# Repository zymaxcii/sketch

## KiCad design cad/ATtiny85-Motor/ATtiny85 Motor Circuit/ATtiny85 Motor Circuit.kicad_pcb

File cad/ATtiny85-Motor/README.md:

# ATtiny85-Motor

These are all the files that I used to make a ATtiny85 circuit that controls a motor's speed using a potentiometer, and also has indicator LEDs to qualitatively show the speed as you turn the potentiometer.

One thing to note is that for some reason the footprint for the diode D1 is backwards in KiCAD so when I first tried building this circuit the transistor would get very hot and after reversing the diode, the circuit worked properly.

I made a short youtube video to demonstrate this: https://www.youtube.com/watch?v=jHjCyNegOxA

https://github.com/The-Invent0r/ATtiny85-Motor/tree/main

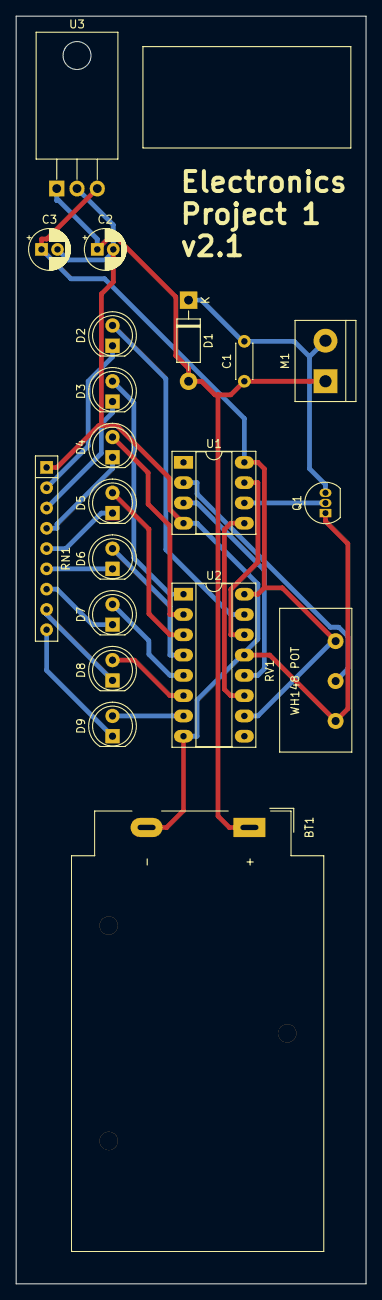
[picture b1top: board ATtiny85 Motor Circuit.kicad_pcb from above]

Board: 2 copper layers, 43.8 x 158.8 mm, 20 parts (0 on the bottom side), 25 nets.

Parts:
BT1: Battery_Cell; BatteryHolder_MPD_BA9VPC_1xPP3
C1: C; C_Disc_D4.3mm_W1.9mm_P5.00mm
C2, C3: CP1; CP_Radial_D5.0mm_P2.00mm
D1: DIODE; D_DO-41_SOD81_P10.16mm_Horizontal
D2, D3, D4, D5, D6, D7, D8, D9: LED; LED_D5.0mm
M1: Motor_DC; TerminalBlock_bornier-2_P5.08mm
Q1: 2N7000; TO-92_Inline
RN1: R_Network08; R_Array_SIP9
RV1: R_POT; Potentiometer_WH148
U1: ATtiny85-20PU; DIP-8_W7.62mm_Socket_LongPads
U2: 74HC595; DIP-16_W7.62mm_Socket_LongPads
U3: L7805; TO-220-3_Horizontal_TabDown

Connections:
GND: BT1.2, C2.2, C3.2, Q1.1, RN1.1, RV1.1, U1.4, U2.8, U2.13, U3.2
unnamed: BT1.1, C1.1, C2.1, D1.2, M1.1, U3.1
unnamed: C1.2, D1.1, M1.2, Q1.3
unnamed: D2.1, RN1.2
unnamed: D2.2, U2.15
unnamed: D3.1, RN1.3
unnamed: D3.2, U2.1
unnamed: D4.1, RN1.4
unnamed: D4.2, U2.2
unnamed: D5.1, RN1.5
unnamed: D5.2, U2.3
unnamed: D6.1, RN1.6
unnamed: D6.2, U2.4
unnamed: D7.1, RN1.7
unnamed: D7.2, U2.5
unnamed: D8.1, RN1.8
unnamed: D8.2, U2.6
unnamed: D9.1, RN1.9
unnamed: D9.2, U2.7
unnamed: Q1.2, U1.6
unnamed: RV1.2, U1.2
unnamed: U1.3, U2.12
unnamed: U1.5, U2.11
unnamed: U1.7, U2.14
VCC: C3.1, RV1.3, U1.8, U2.10, U2.16, U3.3

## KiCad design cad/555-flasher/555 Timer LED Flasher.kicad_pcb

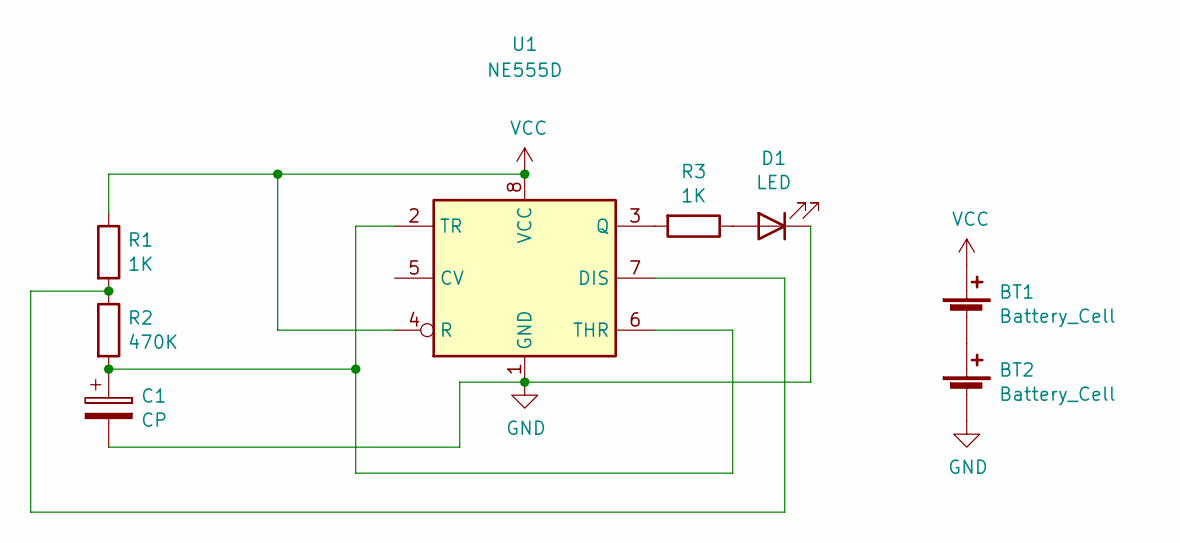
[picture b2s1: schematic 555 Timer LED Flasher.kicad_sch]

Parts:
BT1, BT2: Battery_Cell; BatteryHolder_LINX_BAT-HLD-012-SMT
C1: CP; CP_Elec_4x3
D1: LED; LED_0805_2012Metric
R1, R3: 1K; R_01005_0402Metric
R2: 470K; R_01005_0402Metric
U1: NE555D; SOIC-8_3.9x4.9mm_P1.27mm

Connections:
GND: BT2.2 (-), C1.2, D1.1 (K), U1.1 (GND)
unnamed: BT1.2 (-), BT2.1 (+)
unnamed: C1.1, R2.2, U1.2 (TR), U1.6 (THR)
unnamed: D1.2 (A), R3.1
unnamed: R1.2, R2.1, U1.7 (DIS)
unnamed: R3.2, U1.3 (Q)
VCC: BT1.1 (+), R1.1, U1.4 (R), U1.8 (VCC)

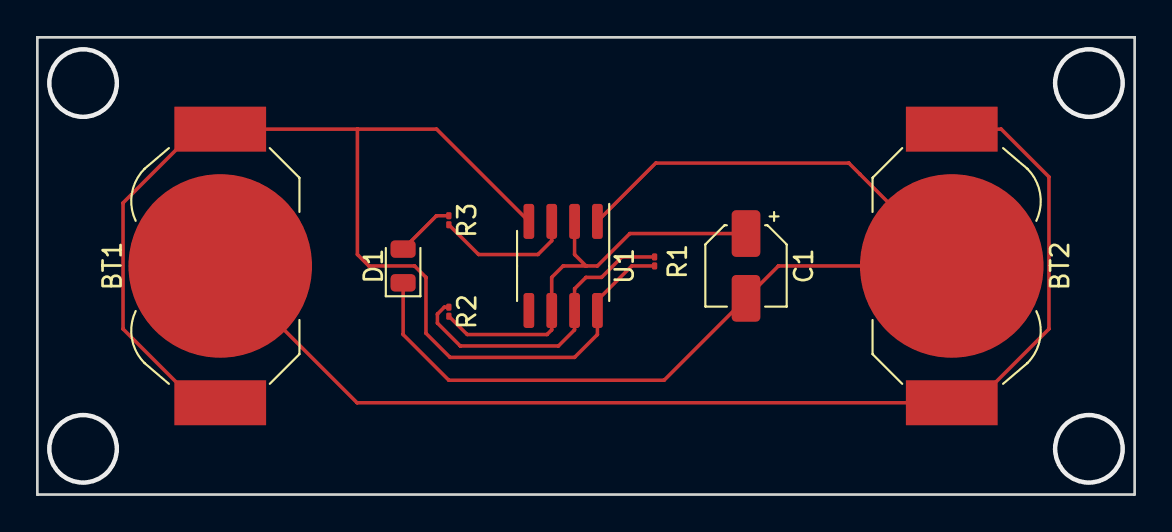
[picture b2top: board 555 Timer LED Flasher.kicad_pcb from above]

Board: 2 copper layers, 61.0 x 25.4 mm, 8 parts (0 on the bottom side), 7 nets.

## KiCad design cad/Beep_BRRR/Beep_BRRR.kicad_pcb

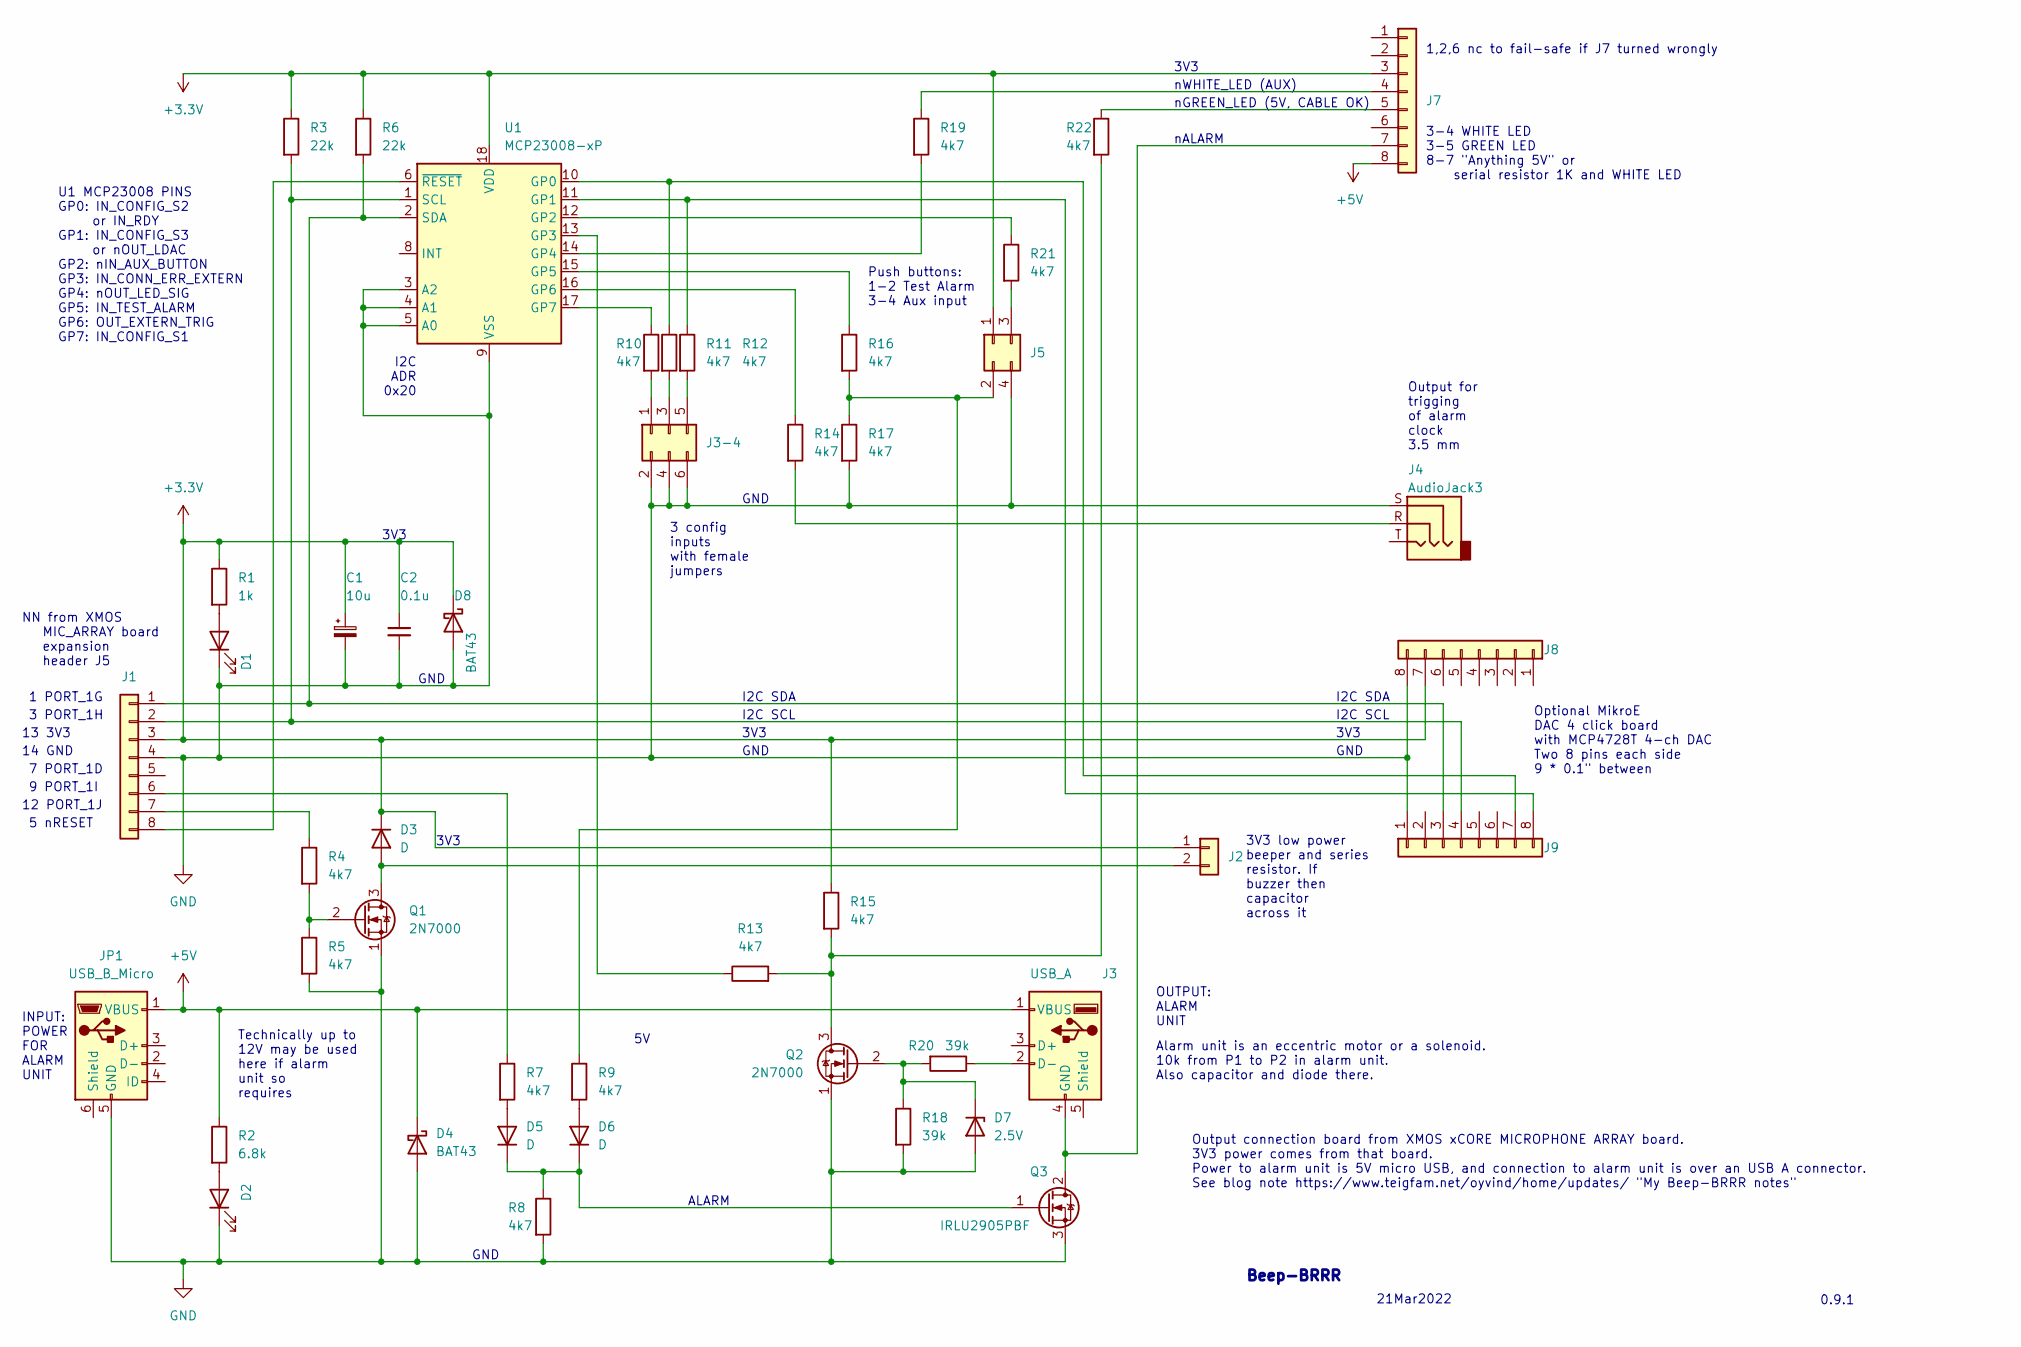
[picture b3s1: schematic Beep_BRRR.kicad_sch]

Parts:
C1: 10u; CP_Radial_D5.0mm_P2.50mm
C2: 0.1u; C_Disc_D3.4mm_W2.1mm_P2.50mm
D1, D2: LED; LED_D3.0mm
D3, D5, D6: D; D_A-405_P2.54mm_Vertical_KathodeUp
D4, D8: BAT43; D_A-405_P2.54mm_Vertical_KathodeUp
D7: 2.5V; D_A-405_P2.54mm_Vertical_KathodeUp
J1: Conn_01x08; PinHeader_1x08_P2.54mm_Vertical
J2: Conn_01x02; PinHeader_1x02_P2.54mm_Vertical
J3: USB_A; USB_A_Molex_67643_Horizontal
J3-4: Conn_02x03_Odd_Even; PinHeader_2x03_P2.54mm_Vertical
J4: AudioJack3; Jack_3.5mm_CUI_SJ1-3533NG_Horizontal_CircularHoles
J5: Conn_02x02_Odd_Even; PinHeader_2x02_P2.54mm_Vertical
J7, J8, J9: Conn_01x08; PinSocket_1x08_P2.54mm_Vertical
JP1: USB_B_Micro; USB_Micro-AB_Molex_47590-0001
Q1, Q2: 2N7000; TO-92_Inline
Q3: IRLU2905PBF; TO-251-3_Vertical
R1: 1k; R_Axial_DIN0204_L3.6mm_D1.6mm_P2.54mm_Vertical
R2: 6.8k; R_Axial_DIN0204_L3.6mm_D1.6mm_P2.54mm_Vertical
R3, R6: 22k; R_Axial_DIN0204_L3.6mm_D1.6mm_P2.54mm_Vertical
R4, R5, R7, R8, R9, R10, R11, R12, R13, R14, R15, R16, R17, R19, R21, R22: 4k7; R_Axial_DIN0204_L3.6mm_D1.6mm_P2.54mm_Vertical
R18, R20: 39k; R_Axial_DIN0204_L3.6mm_D1.6mm_P2.54mm_Vertical
U1: MCP23008-xP; DIP-18_W7.62mm

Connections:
+3V3: C1.1, C2.1, D3.1 (K), D8.1 (K), J1.3, J2.1, J5.1, J7.3, J8.7, R1.1, R3.1, R6.1, R15.1, U1.18 (VDD)
+5V: D4.1 (K), J3.1 (VBUS), J7.8, JP1.1 (VBUS), R2.1
GND: C1.2, C2.2, D1.1 (K), D2.1 (K), D4.2 (A), D7.2 (A), D8.2 (A), J1.4, J3-4.2, J3-4.4, J3-4.6, J4.S, J5.4, J8.8, J9.1, JP1.5 (GND), Q1.1 (S), Q2.1 (S), Q3.3 (S), R5.2, R8.2, R17.2, R18.2, U1.3 (A2), U1.4 (A1), U1.5 (A0), U1.9 (VSS)
unnamed: D1.2 (A), R1.2
unnamed: D2.2 (A), R2.2
unnamed: D3.2 (A), J2.2, Q1.3 (D)
unnamed: D5.1 (K), D6.1 (K), Q3.1 (G), R8.1
unnamed: D5.2 (A), R7.2
unnamed: D6.2 (A), R9.2
unnamed: D7.1 (K), Q2.2 (G), R18.1, R20.2
unnamed: J1.1, J9.3, R6.2, U1.2 (SDA)
unnamed: J1.2, J9.4, R3.2, U1.1 (SCL)
unnamed: J1.6, R7.1
unnamed: J1.7, R4.1
unnamed: J1.8, U1.6 (~RESET)
unnamed: J3-4.1, R10.2
unnamed: J3-4.3, R11.2
unnamed: J3-4.5, R12.2
unnamed: J3.2 (D-), R20.1
unnamed: J3.4 (GND), J7.7, Q3.2 (D)
unnamed: J4.R, R14.2
unnamed: J5.2, R9.1, R16.2, R17.1
unnamed: J5.3, R21.2
unnamed: J7.4, R19.1
unnamed: J7.5, R22.1
unnamed: Q1.2 (G), R4.2, R5.1
unnamed: R10.1, U1.17 (GP7)
unnamed: J9.7, R11.1, U1.10 (GP0)
unnamed: J9.8, R12.1, U1.11 (GP1)
unnamed: R13.1, U1.13 (GP3)
unnamed: Q2.3 (D), R13.2, R15.2, R22.2
unnamed: R14.1, U1.16 (GP6)
unnamed: R16.1, U1.15 (GP5)
unnamed: R19.2, U1.14 (GP4)
unnamed: R21.1, U1.12 (GP2)

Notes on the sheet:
NN from XMOS MIC_ARRAY board expansion header J5
GND
nWHITE_LED (AUX)
21Mar2022
3V3
3-4 WHITE LED 3-5 GREEN LED 8-7 "Anything 5V" or serial resistor 1K and WHITE LED
I2C ADR 0x20
5 nRESET
3 PORT_1H
Output connection board from XMOS xCORE MICROPHONE ARRAY board. 3V3 power comes from that board. Power to alarm unit is 5V micro USB, and connection to alarm unit is over an USB A connector. See blog note https://www.teigfam.net/oyvind/home/updates/ "My Beep-BRRR notes"
I2C SCL
ALARM
3V3 low power beeper and series resistor. If buzzer then capacitor across it
nALARM
1,2,6 nc to fail-safe if J7 turned wrongly
13 3V3
9 PORT_1I
Optional MikroE DAC 4 click board with MCP4728T 4-ch DAC Two 8 pins each side 9 * 0.1" between
Beep-BRRR
14 GND
0.9.1
Output for trigging of alarm clock 3.5 mm
I2C SDA
7 PORT_1D
OUTPUT: ALARM UNIT
Push buttons: 1-2 Test Alarm 3-4 Aux input
3 config inputs with female jumpers
U1 MCP23008 PINS GP0: IN_CONFIG_S2 or IN_RDY GP1: IN_CONFIG_S3 or nOUT_LDAC GP2: nIN_AUX_BUTTON GP3: IN_CONN_ERR_EXTERN GP4: nOUT_LED_SIG GP5: IN_TEST_ALARM GP6: OUT_EXTERN_TRIG GP7: IN_CONFIG_S1
INPUT: POWER FOR ALARM UNIT
12 PORT_1J
Alarm unit is an eccentric motor or a solenoid. 10k from P1 to P2 in alarm unit. Also capacitor and diode there.
Technically up to 12V may be used here if alarm unit so requires
1 PORT_1G
nGREEN_LED (5V, CABLE OK)

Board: 2 copper layers, 46 parts (0 on the bottom side), 35 nets, no tracks yet.

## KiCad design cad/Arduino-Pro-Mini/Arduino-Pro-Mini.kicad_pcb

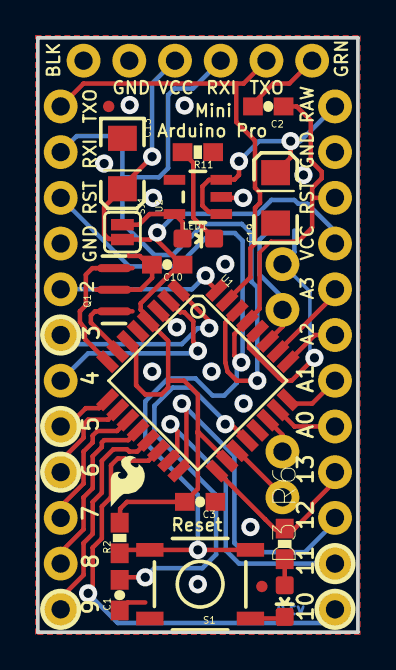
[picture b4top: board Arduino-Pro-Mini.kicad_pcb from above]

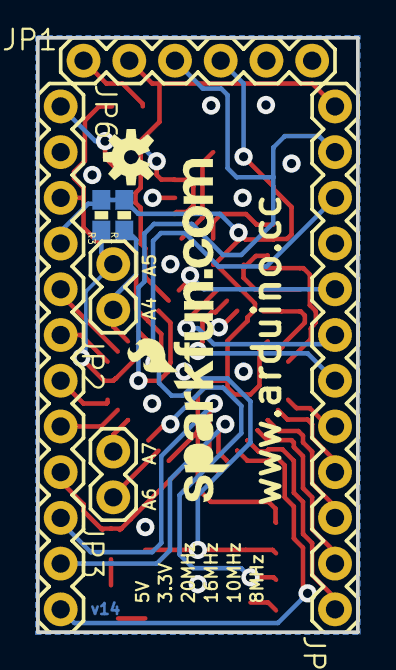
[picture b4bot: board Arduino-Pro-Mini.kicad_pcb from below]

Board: 2 copper layers, 17.8 x 33.0 mm, 29 parts (9 on the bottom side), 33 nets.

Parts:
C1, C2, C3, C10: 0.1uF; 0603-CAP
C13, C19: 10uF; EIA3216
D3: Green; 0603-LED-ALT1
FRAME1: FRAME-LETTER; CREATIVE_COMMONS
JP1: FTDI Basic; 1X06
JP2, JP3: 1X02
JP5, JP8: FIDUCIALUFIDUCIAL; MICRO-FIDUCIAL
JP6, JP7: 1X12
LED1: Red; 0603-LED-ALT1
Q1: 8/16/20MHz; RESONATOR-SMD-1_1
R1, R3: 0603-RES
R2, R11: 10K; 0603-RES
R6: 330; 0603-RES
S1: Reset; TACTILE-SWITCH-SMD-ALT01
SJ1: SJ_2S
U1: ATMEGA328; TQFP32-08
U2: MIC5205; SOT23-5
U$1: LOGO-SFESK; SFE-LOGO-FLAME
U$3: OSHW-LOGOS; OSHW-LOGO-S
U$11: LOGO-SFENEW; SFE-NEW-WEBLOGO

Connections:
A0: JP6.8, U1.23
A1: JP6.7, U1.24
A2: JP6.6, U1.25
A3: JP6.5, U1.26
A4: JP2.1, R1.1, U1.27
A5: JP2.2, R3.1, U1.28
A6: JP3.1, U1.19
A7: JP3.2, U1.22
AREF: C1.2, U1.20
D2: JP7.8, U1.32
D3: JP7.7, U1.1
D4: JP7.6, U1.2
D5: JP7.5, U1.9
D6: JP7.4, U1.10
D7: JP7.3, U1.11
D8: JP7.2, U1.12
D9: JP7.1, U1.13
D10: JP6.12, U1.14
DTR: C2.2, JP1.1
GND: C1.1, C3.1, C10.2, C13.C, C19.C, D3.C, JP1.5, JP1.6, JP6.2, JP7.9, Q1.2, R11.1, S1.1, S1.2, U1.3, U1.5, U1.21, U2.2
MISO: JP6.10, U1.16
MOSI: JP6.11, U1.15
unnamed: Q1.3, U1.8
unnamed: Q1.1, U1.7
unnamed: LED1.A, SJ1.1, U2.5
unnamed: LED1.C, R11.2
unnamed: D3.A, R6.2
RAW: C19.A, JP6.1, U2.1, U2.3
RESET: C2.1, JP6.3, JP7.10, R2.1, S1.3, S1.4, U1.29
RXI: JP1.3, JP7.11, U1.30
SCK: JP6.9, R6.1, U1.17
TXO: JP1.2, JP7.12, U1.31
VCC: C3.2, C10.1, C13.A, JP1.4, JP6.4, R1.2, R2.2, R3.2, SJ1.2, U1.4, U1.6, U1.18

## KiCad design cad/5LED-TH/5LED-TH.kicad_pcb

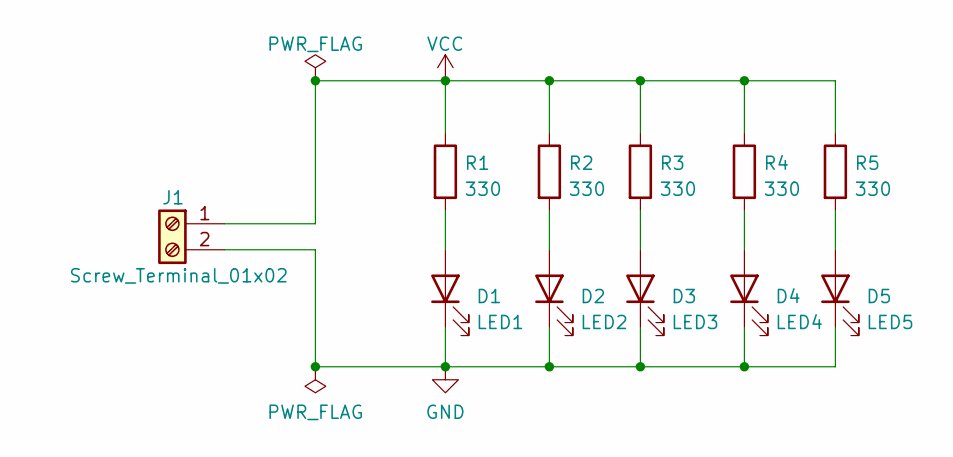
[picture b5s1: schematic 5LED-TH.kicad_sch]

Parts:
D1: LED1; LED_D3.0mm
D2: LED2; LED_D3.0mm
D3: LED3; LED_D3.0mm
D4: LED4; LED_D3.0mm
D5: LED5; LED_D3.0mm
J1: Screw_Terminal_01x02; TerminalBlock_bornier-2_P5.08mm
R1, R2, R3, R4, R5: 330; R_Axial_DIN0204_L3.6mm_D1.6mm_P5.08mm_Horizontal

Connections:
GND: D1.1 (K), D2.1 (K), D3.1 (K), D4.1 (K), D5.1 (K), J1.2
unnamed: D1.2 (A), R1.2
unnamed: D2.2 (A), R2.2
unnamed: D3.2 (A), R3.2
unnamed: D4.2 (A), R4.2
unnamed: D5.2 (A), R5.2
VCC: J1.1, R1.1, R2.1, R3.1, R4.1, R5.1

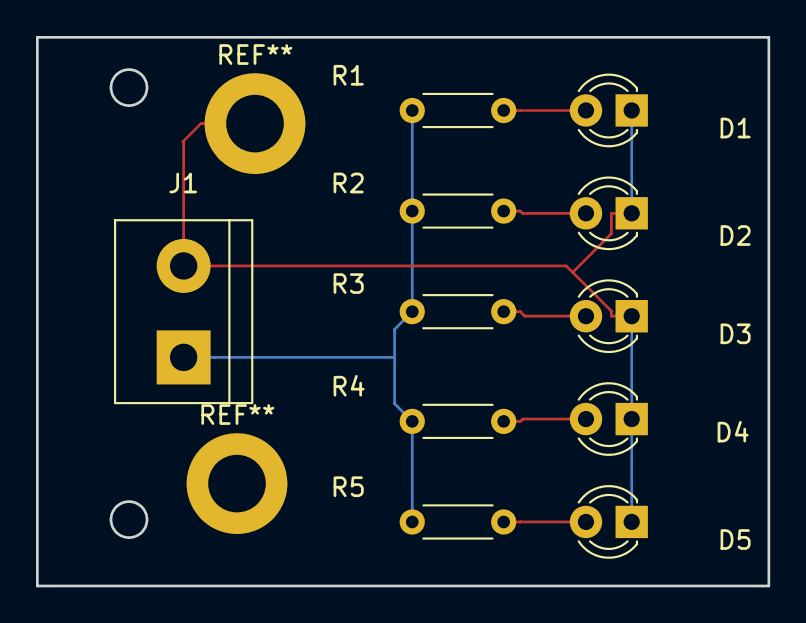
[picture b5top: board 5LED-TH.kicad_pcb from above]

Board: 2 copper layers, 40.6 x 30.5 mm, 11 parts (0 on the bottom side), 7 nets.

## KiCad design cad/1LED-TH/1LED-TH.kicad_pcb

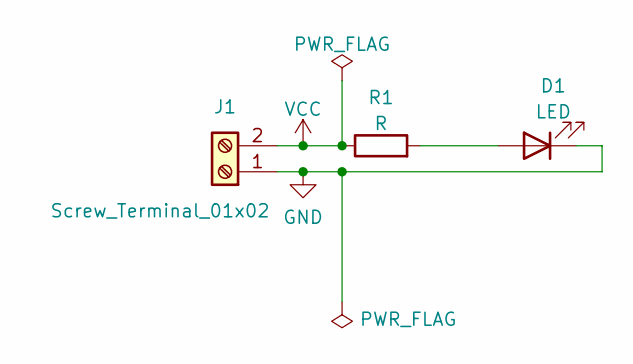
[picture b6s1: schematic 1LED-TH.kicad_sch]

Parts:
D1: LED; LED_D3.0mm
J1: Screw_Terminal_01x02; TerminalBlock_bornier-2_P5.08mm
R1: R; R_Axial_DIN0204_L3.6mm_D1.6mm_P5.08mm_Horizontal

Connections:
GND: D1.1 (K), J1.1
unnamed: D1.2 (A), R1.2
VCC: J1.2, R1.1

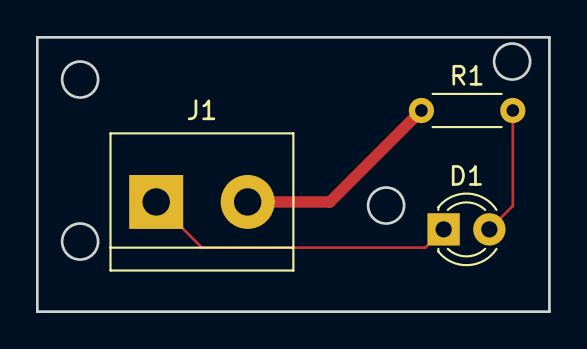
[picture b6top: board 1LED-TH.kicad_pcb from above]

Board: 2 copper layers, 28.4 x 15.2 mm, 3 parts (0 on the bottom side), 3 nets.

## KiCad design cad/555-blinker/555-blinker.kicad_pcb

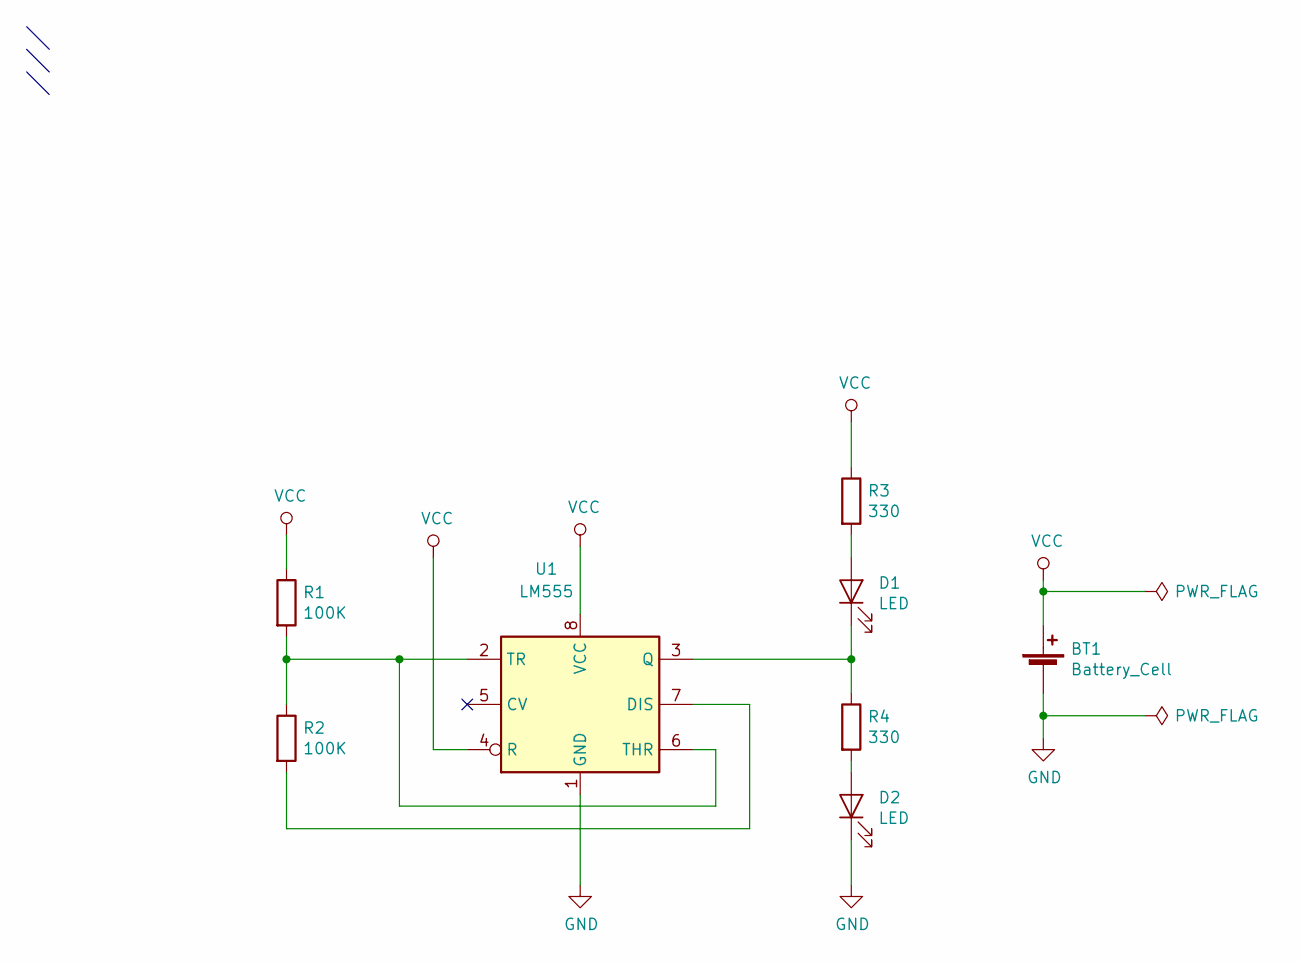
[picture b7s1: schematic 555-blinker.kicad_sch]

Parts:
BT1: Battery_Cell; PinHeader_1x02_P2.54mm_Horizontal
D1, D2: LED; LED_D3.0mm
R1, R2: 100K; R_Axial_DIN0204_L3.6mm_D1.6mm_P5.08mm_Horizontal
R3, R4: 330; R_Axial_DIN0204_L3.6mm_D1.6mm_P5.08mm_Horizontal
U1: LM555; DIP-8_W7.62mm

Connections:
GND: BT1.2 (-), D2.1 (K), U1.1 (GND)
unnamed: D1.1 (K), R4.1, U1.3 (Q)
unnamed: D1.2 (A), R3.2
unnamed: D2.2 (A), R4.2
unnamed: R1.2, R2.1, U1.2 (TR), U1.6 (THR)
unnamed: R2.2, U1.7 (DIS)
VCC: BT1.1 (+), R1.1, R3.1, U1.4 (R), U1.8 (VCC)

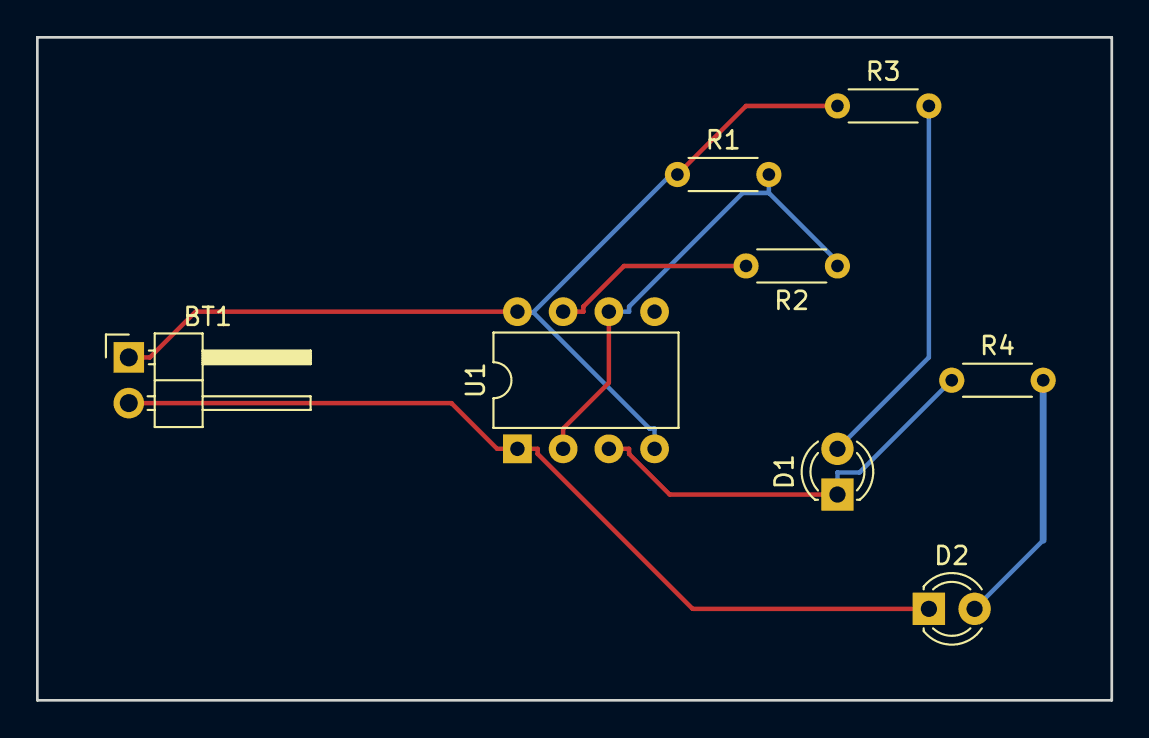
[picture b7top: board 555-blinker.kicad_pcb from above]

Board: 2 copper layers, 59.7 x 36.8 mm, 8 parts (0 on the bottom side), 7 nets.

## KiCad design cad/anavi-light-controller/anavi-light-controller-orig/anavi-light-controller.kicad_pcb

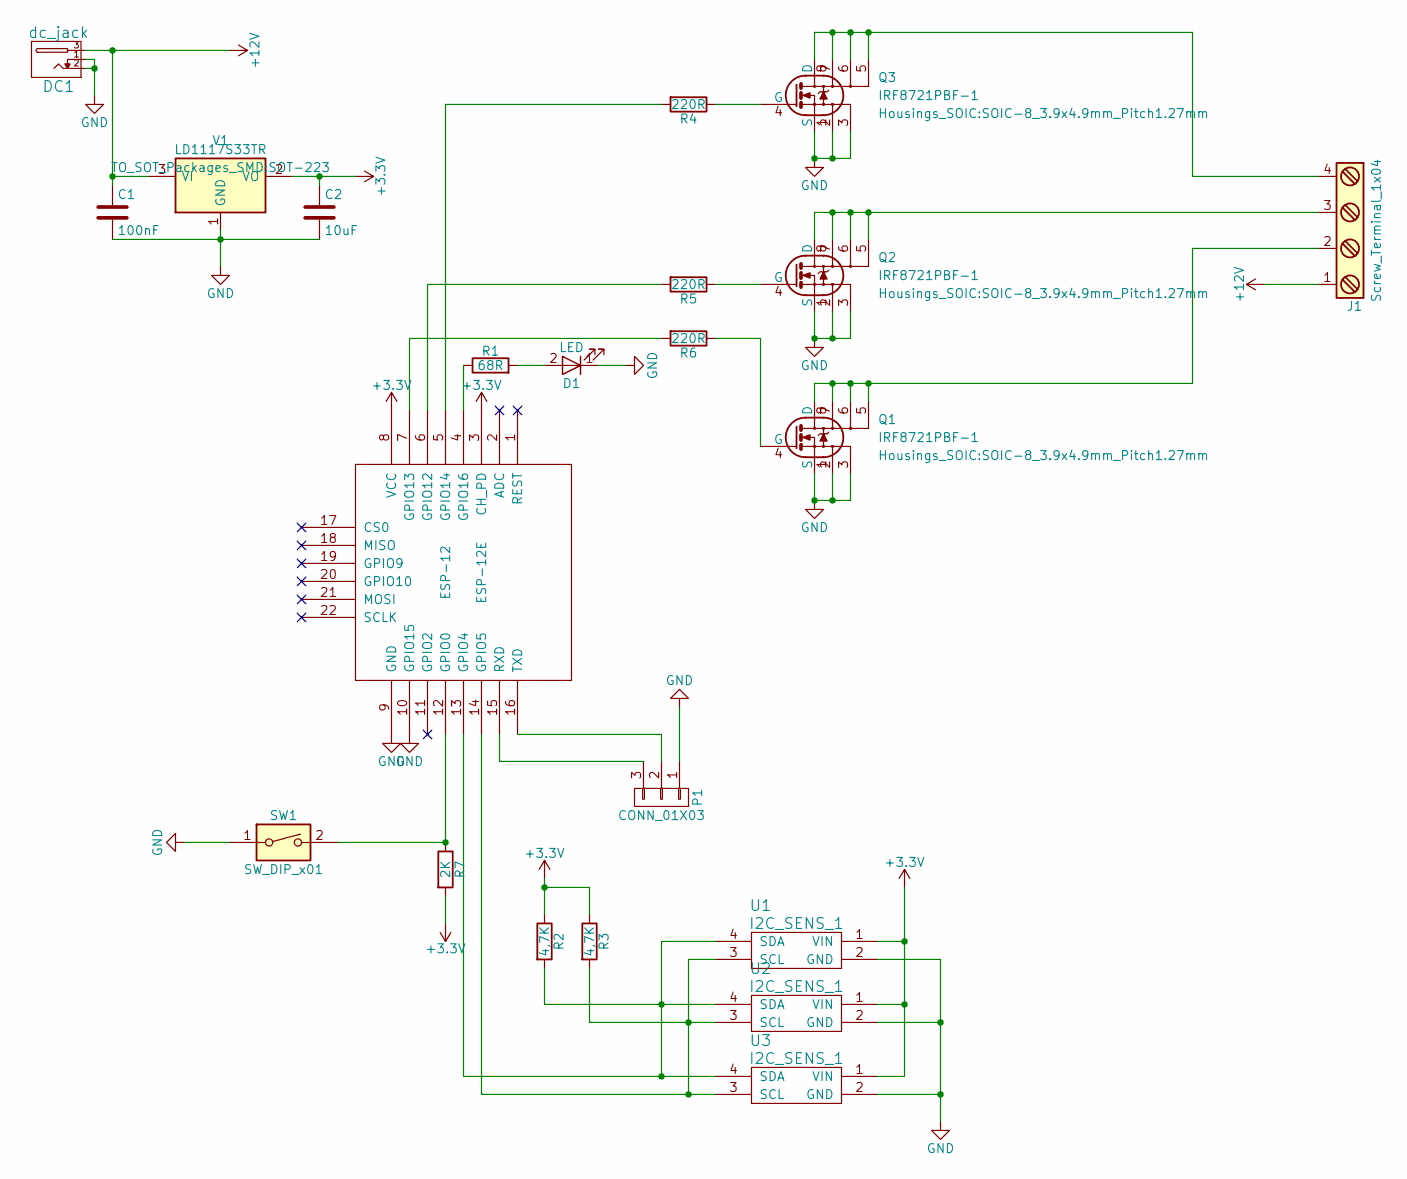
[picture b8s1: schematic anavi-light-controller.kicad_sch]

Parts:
C1: 100nF; C_0603_HandSoldering
C2: 10uF; C_0805_HandSoldering
D1: LED; LED_1206
DC1: dc_jack; dc_socket
ESP-12: ESP-12E; ESP-12E_SMD
J1: Screw_Terminal_1x04; TerminalBlock_Pheonix_MKDS1.5-4pol
P1: CONN_01X03; Pin_Header_Straight_1x03
Q1, Q2, Q3: IRF8721PBF-1; SOIC-8_3.9x4.9mm_Pitch1.27mm
R1: 68R; R_0603_HandSoldering
R2, R3: 4,7K; R_0603_HandSoldering
R4, R5, R6: 220R; R_0603_HandSoldering
R7: 2K; C_0603_HandSoldering
SW1: SW_DIP_x01; SW_PUSH_6mm_h4.3mm
U1, U2, U3: I2C_SENS_1; Pin_Header_Straight_1x04
V1: LD1117S33TR; SOT-223

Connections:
+3V3: C2.1, ESP-12.3 (CH_PD), ESP-12.8 (VCC), R2.1, R3.1, R7.2, U1.1 (VIN), U2.1 (VIN), U3.1 (VIN), V1.2 (VO)
+12V: C1.1, DC1.3, J1.1, V1.3 (VI)
GND: C1.2, C2.2, D1.1 (K), DC1.1, DC1.2, ESP-12.9 (GND), ESP-12.10 (GPIO15), P1.1, Q1.1 (S), Q1.2, Q1.3, Q2.1 (S), Q2.2, Q2.3, Q3.1 (S), Q3.2, Q3.3, SW1.1, U1.2 (GND), U2.2 (GND), U3.2 (GND), V1.1 (GND)
unnamed: D1.2 (A), R1.2
unnamed: ESP-12.4 (GPIO16), R1.1
unnamed: ESP-12.5 (GPIO14), R4.2
unnamed: ESP-12.6 (GPIO12), R5.2
unnamed: ESP-12.7 (GPIO13), R6.2
unnamed: ESP-12.12 (GPIO0), R7.1, SW1.2
unnamed: ESP-12.13 (GPIO4), R2.2, U1.4 (SDA), U2.4 (SDA), U3.4 (SDA)
unnamed: ESP-12.14 (GPIO5), R3.2, U1.3 (SCL), U2.3 (SCL), U3.3 (SCL)
unnamed: ESP-12.15 (RXD), P1.3
unnamed: ESP-12.16 (TXD), P1.2
unnamed: J1.2, Q1.5, Q1.6, Q1.7, Q1.8 (D)
unnamed: J1.3, Q2.5, Q2.6, Q2.7, Q2.8 (D)
unnamed: J1.4, Q3.5, Q3.6, Q3.7, Q3.8 (D)
unnamed: Q1.4 (G), R6.1
unnamed: Q2.4 (G), R5.1
unnamed: Q3.4 (G), R4.1

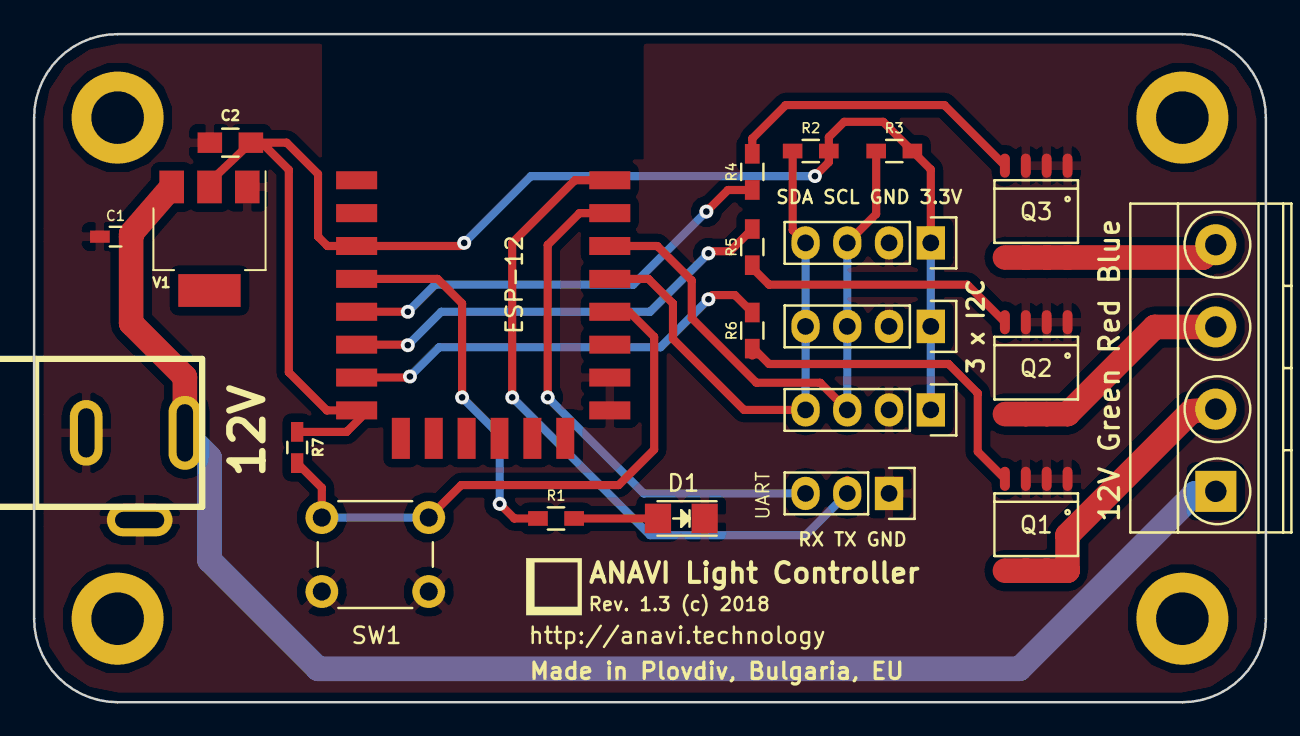
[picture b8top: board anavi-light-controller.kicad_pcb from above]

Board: 2 copper layers, 74.9 x 40.6 mm, 22 parts (0 on the bottom side), 19 nets.

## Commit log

2022-02-16 added 3 7 segment sketches
2022-03-13 added SevSeg library
2022-03-13 added Santos folder
2022-03-14 added dot matrix and oled libraries
2022-03-15 added rfid and ds18b20
2022-03-16 added dallas temperature
2022-03-30 added project-book
2022-03-30 modified project book code round 1
2022-03-30 added datasheet and note folders
2022-03-30 deleted some sketch files at root
2022-03-30 added datasheet folder content
2022-03-30 added seven-segment display pdf
2022-03-30 added Servo library
2022-03-31 round 2 debugging buzzer
2022-04-05 modified pinwheel.ino
2022-04-12 work on RTC...
2022-04-18 added esp32 folder
2022-04-18 fixed DeepSleep
2022-04-20 added codes for 8led module
2022-04-21 fixed traffic light 4 way
2022-04-26 modifed various 8led sketches
2022-04-27 deleted note folder
2022-04-27 sync project-book folder using FreeFileSync
2022-04-27 deleted doc and tmp folders in project-book
2022-04-28 added 8ledsr sketches
2022-05-03 modified 7seg_ sketches
2022-05-04 clean up local files on asrock
2022-05-11 simplify santos folder
2022-05-12 continue work on santos
2022-05-13 worked on pir...
2022-05-13 changed folder santos to sensor
2022-05-13 changed folder project-book to basic
2022-05-17 modified reed switch and rtc
2022-05-18 modified motion_detector.ino
2022-05-19 cleared ultra64gb transfer folder
2022-05-27 added sketches from FF KIV
2022-07-05 added some sketches from FF KIV
2022-07-07 work on servo_miniRobot. Not working yet
2022-07-08 miniRobot working now
2022-07-14 edit switch_polling sketches
2022-07-15 edit more 7seg4d sketches
2022-07-20 edit some 7seg4d sketches
2022-07-21 edit tm1637 sketches
2022-07-25 added some sketches from ultra64gb stick
2022-07-26 edit potbSerialUpdater and its pde
2022-07-27 added more sketches from ultra64gb stick
2022-07-28 added serial_list.pde
2022-07-29 edit some attiny85 sketches
2022-07-29 added awg.gif
2022-07-29 added 2004 LCD datasheet
2022-07-29 added Bartnik
2022-07-29 added sunfounder
2022-07-29 added curio res
2022-07-29 added elegoo
2022-08-01 edit 7seg4dI2C_alarmClock.ino
2022-08-02 edit 7seg4dI2C_alarmClock-eeprom.ino
2022-08-03 edit buzzer sketches
2022-08-03 clean up mega storage
2022-08-04 test git with 4n35_led.ino
2022-08-04 more editing and cleaning
2022-08-05 clean up mega and added more here
2022-08-05 compile ino in a hurry
2022-08-07 edit some sketches on hp all-in-1
2022-08-08 last edit before moving on to hardware folder creations
2022-08-08 added tm1638.ino
2022-08-09 moved ir sketches to ir folder
2022-08-10 some clean up
2022-08-10 edit some ir sketches
2022-08-10 work on ir sketches
2022-08-10 switch to IRremote lib 2.5
2022-08-10 added 8led folder
2022-08-10 added more folder
2022-08-10 added lcd folder
2022-08-11 added ir sketches from dronebot
2022-08-16 added fastled and neopixels sketches
2022-08-17 work on ir send
2022-08-26 fixed IRremote hex code 0
2022-08-30 debug ir_powerOnOff
2022-09-08 created panTilt folder and others
2022-09-08 added pid folder...
2022-09-09 created some more folders
2022-09-09 clean up best folder
2022-09-09 finished cleaning up best folder
2022-09-10 edited some IRremote stuff
2022-09-14 rename files in datasheet round 1
2022-09-14 clean up basic folder 20220914
2022-09-14 a bit more cleanup
2022-09-14 clean up sunfounder folder, round 1
2022-09-14 clean up sunfounder, round 2
2022-09-15 work on LCD 1602
2022-09-24 added url to ledstrip
2022-09-25 modified lcd1602
2022-09-27 worked on lcdi2c sketches
2022-09-30 further work on lcdi2c sketches
2022-10-05 added sketches from ultra64gb stick
2022-10-06 added sketches from Manjaro Cinnamon
2022-10-07 move lm35 schematics
2022-10-18 clean up tm1638 folder
2022-10-20 work on tm1638 round 1
2022-10-20 clean up tm1638 folder, round 2
2022-10-21 test git integrity on tm1638_demo.ino
2022-10-21 played with tm1638
2022-10-21 played with elegoo sensors
2022-10-25 cleaned up lm35 codes
2022-10-25 worked on lm35 folder
2022-10-26 cleaned up ledstrip folder
2022-10-28 tidy up folders
2022-10-28 minor change
2022-10-28 reorder tm1637
2022-10-30 modified led codes to accomodate the 8 led module
2022-10-31 worked on 8 led module
2022-11-01 modified 4N35.ino
2022-11-01 added 4n35.png
2022-11-03 Changed CS to pin D10 for MAX7219
2022-11-03 commit from stash stack:max7219_printText.ino
2022-11-06 some cleanup
2022-11-06 small cap for all folders
2022-11-06 restore ir folder from dht folder
2022-11-06 move files to their respective folders
2022-11-08 learning LedControl library
2022-11-09 worked on LedControl
2022-11-09 clean up max7219 codes
2022-11-09 next to work on max7219_clock
2022-11-11 added ds3231 sketches
2022-11-11 added ds3231_sqwInt.ino
2022-11-12 added ds3231 oled sketch
2022-11-13 added max7219 sketches from Mario
2022-11-14 modified eeprom sketches
2022-11-14 added more eeprom sketches
2022-11-14 more max7219 sketches
2022-11-15 further work on max7219 sketches
2022-11-18 played with max7219 sketches with Hantek scope. Round 1
2022-11-19 added urtclib
2022-11-21 clean up some newly added ds3231 sketches
2022-11-22 added LcdMenu
2022-11-26 added 12 max7219
2022-11-27 prepared to work on ds3231
2022-11-28 added oled-ds3231 sketches
2022-11-29 work on max7219 8-digit 7-segment display
2022-12-10 added sketches from transfer folder
2022-12-30 added audio-jack.pdf
2023-01-03 after git stash pop from mj gnome stick
2023-01-05 clean up some rtc 3231 sketches
2023-01-13 added kicad stuff in cad folder
2023-01-17 more kicad learning
2023-01-17 learn v to place via in stop light
2023-01-19 added stop light tht and smd folders
2023-01-26 added grio_board in cad folder
2023-01-26 worked on ds3231
2023-01-27 clean up rtc codes on 20230127
2023-01-28 migrate to kicad 6
2023-01-30 added now.ino from ds3231 library
2023-01-30 test GR_IO_Board to kicad 6
2023-01-30 modify EEprom file name
2023-01-31 first use of IDE 2.0 on asrock
2023-01-31 added rtclib to file name
2023-02-01 deleted rtc sketches that fail to compile
2023-02-02 clean up lcd folder
2023-02-06 attempt to install freeroute plugin in kicad 6
2023-02-06 freeroute requires jre 17
2023-02-07 testing lcd and lcdi2c on 20220207
2023-02-10 clean up piezo folder
2023-02-11 added pcm stuff
2023-02-11 added pcm_testSample.ino
2023-02-13 modified buzzer_tone
2023-02-14 final clean up of piezo codes
2023-02-14 added 2N2222 to drive speaker
2023-02-15 piezo folder clean up
2023-02-16 work on keypad folder
2023-02-16 merged and deleted sensor folder
2023-02-16 merged all led related folders
2023-02-16 deleted
2023-02-17 explore calculator sketches in keypad folder
2023-02-18 added another calculator sketch
2023-02-20 create new kicad project 8-Led
2023-02-21 more problems with DS3231 library
2023-02-21 local ds3231 library not working
2023-02-21 kicad file
2023-02-21 added U8glib
2023-02-22 fixed ds3231 pin swapping
2023-02-22 added u8g2-based clock
2023-02-22 kicad 8Led reduced board size
2023-02-22 edit oled_U8g2_clock_v1.ino
2023-02-23 clean up oled_U8g2_clockV4.ino
2023-02-23 edited oled_U8g2_clockV6.ino
2023-02-24 played with oled_U8g2_clockV7.ino
2023-02-27 testing tft sketches
2023-02-27 added oled_re_pong.ino
2023-02-27 added tft_showBMP.ino
2023-02-27 clean up sketches from Maximilian Hentsch
2023-02-28 make oled_pong works
2023-03-02 added ADKeyboard schematics
2023-03-03 learn add lines in kicad for 8Led
2023-03-03 learn add lines press i
2023-03-04 added function and maker folders
2023-03-04 further clean up
2023-03-06 tidy up function folder
2023-03-08 added csedunio
2023-03-08 added anavi-light-controller
2023-03-11 added stuff from ultra64gb
2023-03-22 added ammeter
2023-03-24 added pcbway template
2023-03-31 restart my arduino journey
2023-04-15 added Joule thief.jpg
2023-04-15 added fan circuit.jpg
2023-04-18 work on sleep.ino using jeelib library
2023-05-10 added kicad project 5LED-TH
2023-05-11 added 1LED-TH in cad folder
2023-05-11 learn footprint browser
2023-05-13 added vcc and gnd planes to 1LED
2023-05-13 added dimension lines
2023-05-14 added mounting holes
2023-05-25 added pro mini.png
2023-05-25 added 1LED in cad
2023-05-25 added 1LED
2023-05-25 added Arduino-Pro-Mini
2023-05-25 added Arduino-Pro-Mini docs
2023-05-26 clean up download and transfer folders
2023-05-26 deleted datasheet
2023-05-31 added switch box
2023-06-05 added ATtiny85-Motor in cad folder
2023-06-07 added pi-pico folder
2023-06-12 added trafficLight.py
2023-06-12 modified trafficLight.py to add pedestrian crossing LED
2023-06-13 added pi pico reaction games
2023-07-20 added url to pong sketch
2023-08-11 added fan motor wiring
2023-08-25 added note js stuff
2023-11-06 added bits and pieces
2024-01-12 deleted schematics dir
2024-03-08 setup Nano with the 8-led-module
2024-03-08 added some ATting stuff

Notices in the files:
cad/anavi-light-controller/anavi-light-controller-orig/anavi-light-controller.kicad_pcb:
Rev. 1.3 (c) 2018
parts and their libraries:
HTTP://CREATIVECOMMONS.ORG/LICENSES/BY-SA/3.0
RELEASED UNDER THE CREATIVE COMMONS ATTRIBUTION SHARE-ALIKE 3.0 LICENSE
